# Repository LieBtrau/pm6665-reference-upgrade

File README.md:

# pm6665-reference-upgrade
Improved 10MHz oscillator for the PM6665 frequency counter.

The basic version of the PM6665 has a tunable Pierce oscillator with a 74HCU04.  
20 years later and with a **€5 budget**, we can do much better than that.  
The [hardware](../../wiki/BRD161205 R0) uses a VCTCXO with a **frequency stability of 500ppb** over the -40°C..85°C range.  The potmeter allows to calibrate for the initial 2ppm frequency offset of the oscillator.  

# Calibration
* For calibrating you'll need a frequency source that is even better than this oscillator.  Preferably, that reference is also cheap.  The **GPSDO** (GPS disciplined oscillator) is a widely used solution.  If you want it cheaper (and with less accuracy), you can take the 1PPS output of a Quectel L86-M33 GPS module.  This 1Hz pulse has a < 15ns accuracy, which is 15ppb.  
* **Yearly calibration** is needed, because the frequency of the VCTCXO will drift away by 1ppm/year.
*  [Some cheap custom hardware](../../wiki/BRD161206 R0) has been designed that allows to calibrate the oscillator.

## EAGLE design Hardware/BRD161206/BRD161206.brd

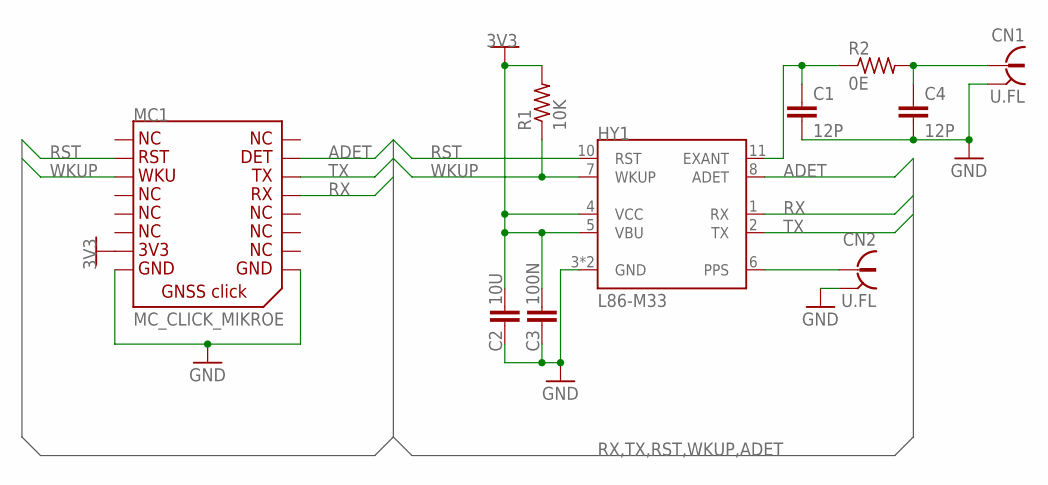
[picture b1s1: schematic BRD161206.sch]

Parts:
C1, C4: 12P; CA_0603
C2: 10U; CA_1206
C3: 100N; CA_1206
CN1, CN2: U.FL; CN_RF_U.FL_MALE
HY1: L86-M33; HY_GNSS_L86-M33
MC1: MC_CLICK_MIKROE
R1: 10K; RE_1206
R2: 0E; RE_0603

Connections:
3V3: C2.1, C3.1, HY1.4 (VCC), HY1.5 (VBU), MC1.P$7, R1.2
ADET: HY1.8 (ADET), MC1.P$15
GND: C1.2, C2.2, C3.2, C4.2, CN1.2A (OUTER), CN1.2B (OUTER), CN2.2A (OUTER), CN2.2B (OUTER), HY1.3 (GND), HY1.12 (GND), MC1.P$8 (8), MC1.P$9
unnamed: C1.1, HY1.11 (EXANT), R2.1
unnamed: CN2.1 (INNER), HY1.6 (PPS)
unnamed: C4.1, CN1.1 (INNER), R2.2
RST: HY1.10 (RST), MC1.P$2
RX: HY1.1 (RX), MC1.P$13
TX: HY1.2 (TX), MC1.P$14
WKUP: HY1.7 (WKUP), MC1.P$3, R1.1

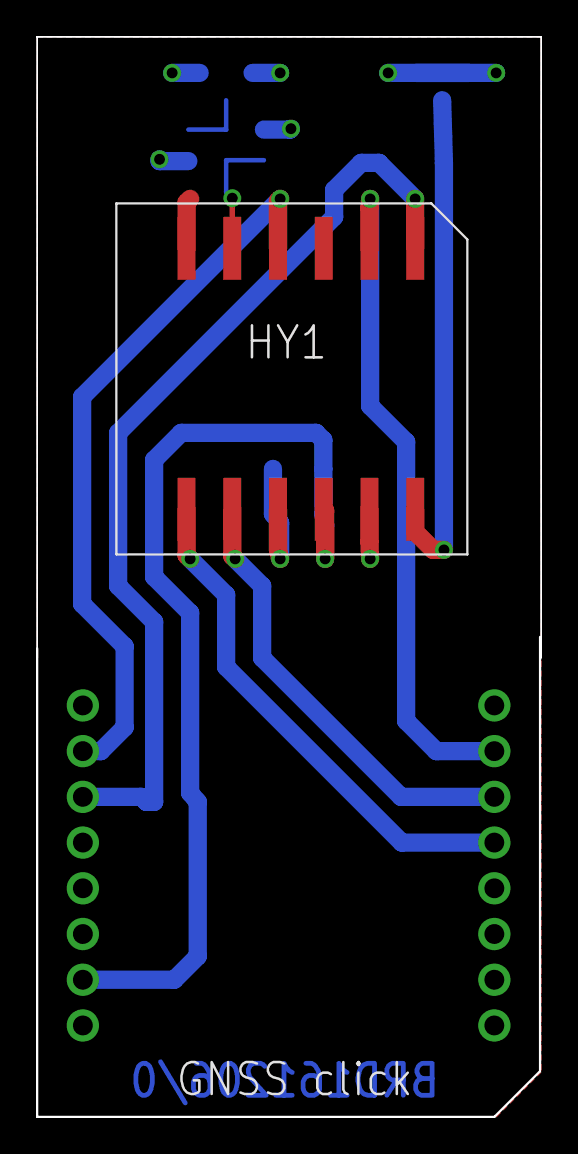
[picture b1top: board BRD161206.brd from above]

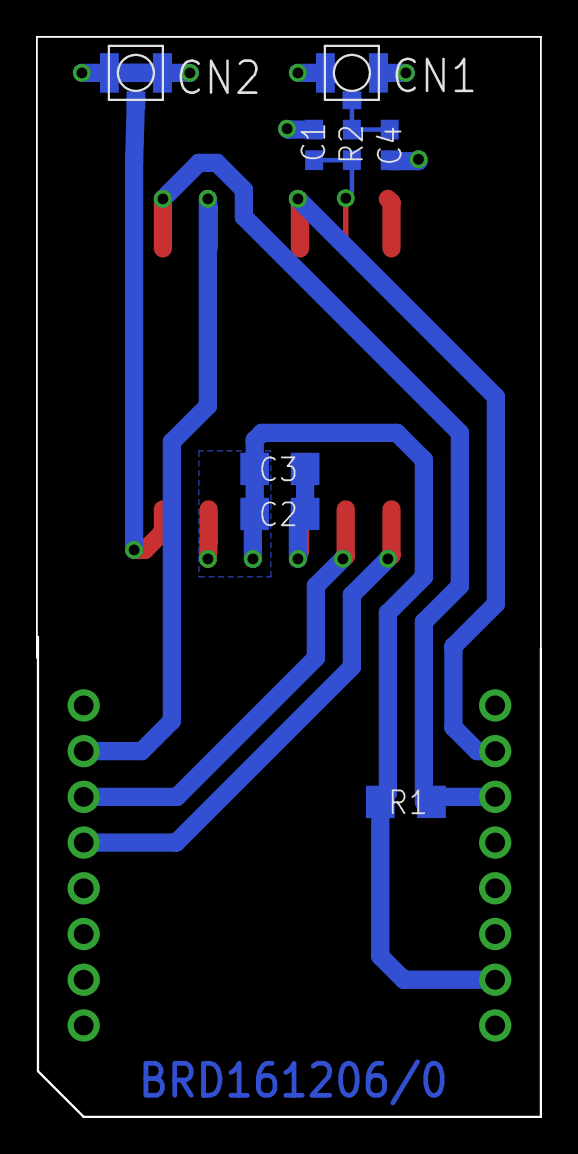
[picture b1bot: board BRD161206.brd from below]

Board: 2 copper layers, 28.0 x 60.0 mm, 11 parts (8 on the bottom side), 10 nets.

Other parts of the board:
U$2: MC_FRAME_A5

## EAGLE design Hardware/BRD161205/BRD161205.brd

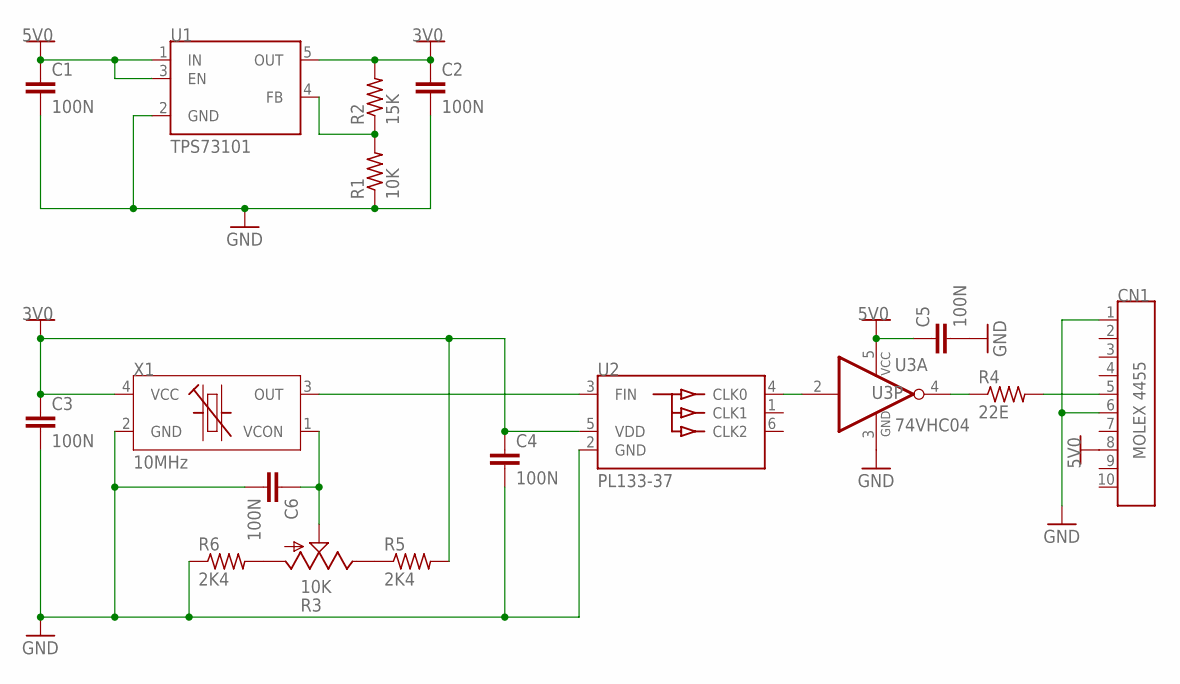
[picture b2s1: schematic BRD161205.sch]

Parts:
C1, C2, C3, C4, C5, C6: 100N; CA_1206
CN1: MOLEX 4455; CN_HDR1X10_90D_P254_MOLEX_4455
R1: 10K; RE_1206
R2: 15K; RE_1206
R3: 10K; RE_TRIM_TH_90D_P25
R4: 22E; RE_1206
R5, R6: 2K4; RE_1206
U1: TPS73101; SC_SOT23-5
U2: PL133-37; SC_SOT23-6
U3: 74VHC04; SC_SOT23-5
X1: 10MHz; XT_3225

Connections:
3V0: C2.1, C3.1, C4.1, R2.2, R5.2, U1.5 (OUT), U2.5 (VDD), X1.4 (VCC)
5V0: C1.1, C5.1, CN1.8, U1.1 (IN), U1.3 (EN), U3.5 (VCC)
GND: C1.2, C2.2, C3.2, C4.2, C5.2, C6.2, CN1.1, CN1.6, R1.1, R6.1, U1.2 (GND), U2.2 (GND), U3.3 (GND), X1.2 (GND)
unnamed: R1.2, R2.1, U1.4 (FB)
unnamed: C6.1, R3.2, X1.1 (VCON)
unnamed: U2.4 (CLK0), U3.2 (I)
unnamed: U2.3 (FIN), X1.3 (OUT)
unnamed: R4.1, U3.4 (O)
unnamed: CN1.5, R4.2
unnamed: R3.3, R5.1
unnamed: R3.1, R6.2

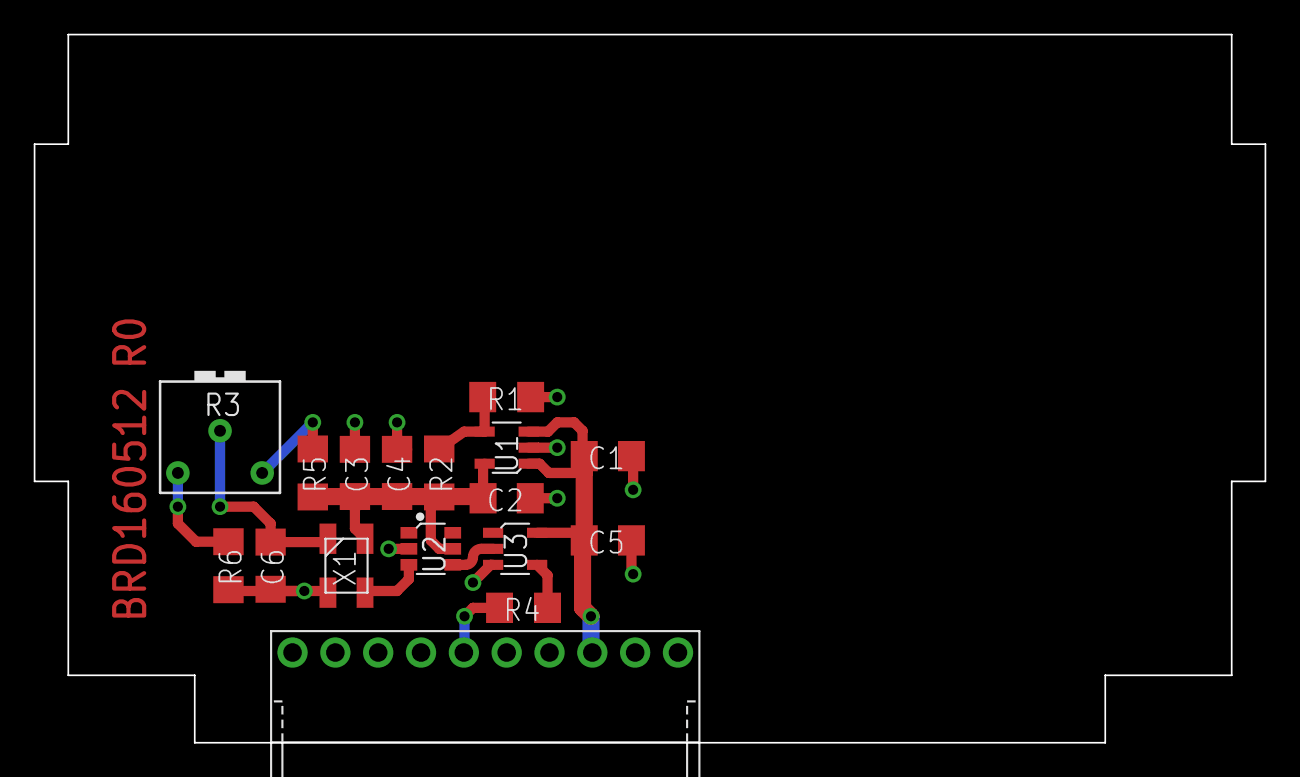
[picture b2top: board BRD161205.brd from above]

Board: 2 copper layers, 73.0 x 42.0 mm, 19 parts (0 on the bottom side), 11 nets.

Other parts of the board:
DRILEGEND: DRILEGEND
U$6: FR_FRAME_A5

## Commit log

2016-12-10 fully routed, not cleaned up
2016-12-11 BRD161205 R0
2016-12-11 Adding gitignore
2016-12-11 Adding detailed info about the project
2016-12-20 BRD161206 R00.0x
2016-12-20 Adding info about calibrating the oscillator
2016-12-23 Adding BRD number
